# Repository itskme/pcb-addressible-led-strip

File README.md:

This is my first independent design using kiCAD. No tutorals or anything like that. I have not written software for this project however you should be able to adapt any rgb matrix program to control this board as-is, or modify the physical connections yourself if you want!

Gerbers are in the project directory

Enjoy :)

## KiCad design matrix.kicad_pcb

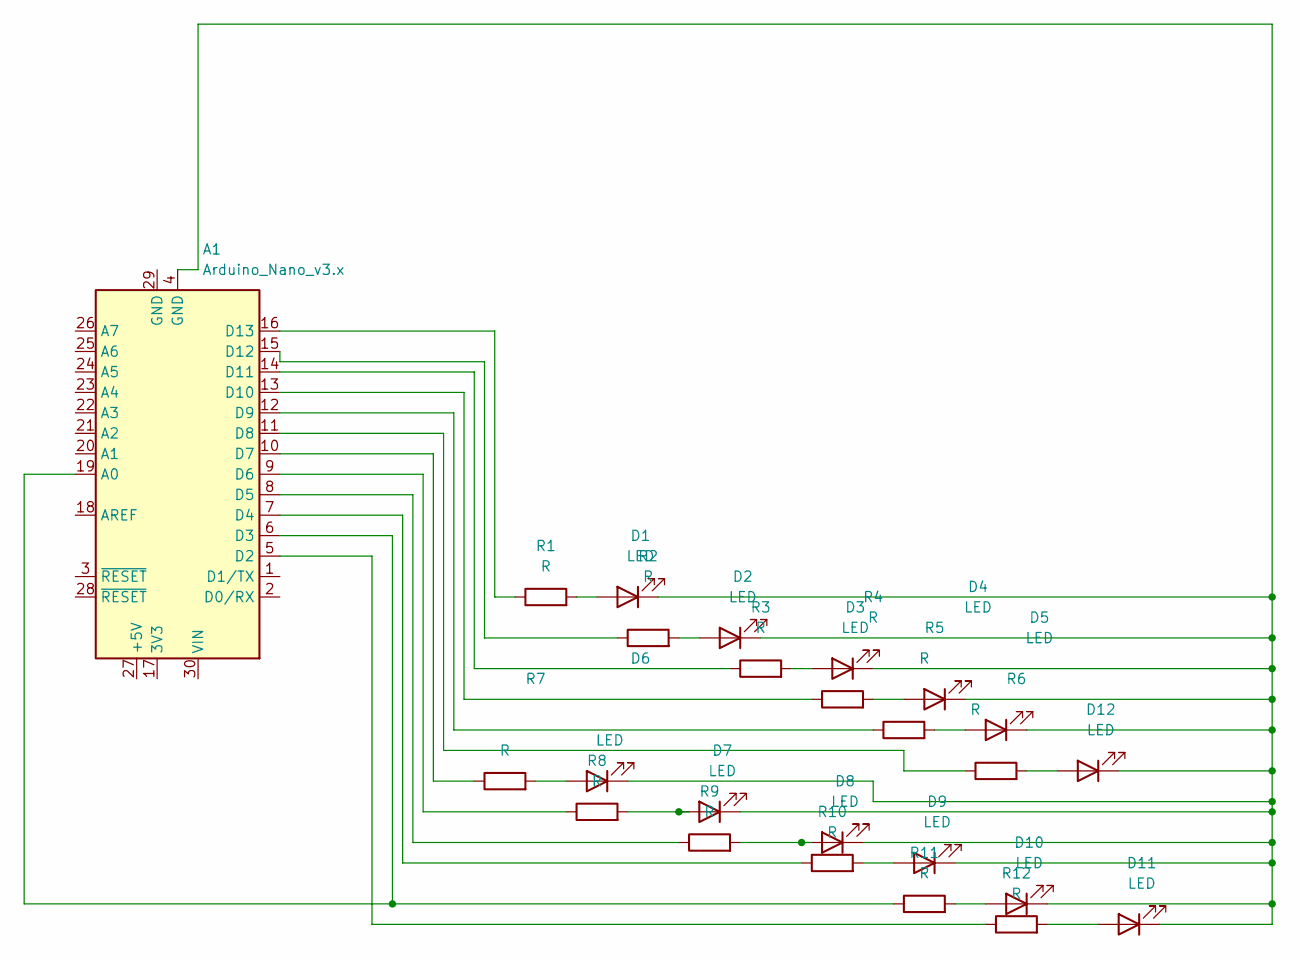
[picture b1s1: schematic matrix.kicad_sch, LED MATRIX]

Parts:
A1: Arduino_Nano_v3.x; Arduino_Nano
D1, D2, D3, D4, D5, D6, D7, D8, D9, D10, D11, D12: LED; LED_0402_1005Metric
R1, R2, R3, R4, R5, R6, R7, R8, R9, R10, R11, R12: R; R_01005_0402Metric

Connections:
unnamed: A1.6 (D3), A1.19 (A0), R11.1
unnamed: A1.5 (D2), R12.1
unnamed: A1.7 (D4), R10.1
unnamed: A1.8 (D5), R9.1
unnamed: A1.9 (D6), R8.1
unnamed: A1.10 (D7), R7.1
unnamed: A1.11 (D8), R6.1
unnamed: A1.12 (D9), R5.1
unnamed: A1.13 (D10), R4.1
unnamed: A1.14 (D11), R3.1
unnamed: A1.15 (D12), R2.1
unnamed: A1.16 (D13), R1.1
unnamed: D1.2 (A), R1.2
unnamed: A1.4 (GND), D1.1 (K), D2.1 (K), D3.1 (K), D4.1 (K), D5.1 (K), D6.1 (K), D7.1 (K), D8.1 (K), D9.1 (K), D10.1 (K), D11.1 (K), D12.1 (K)
unnamed: D2.2 (A), R2.2
unnamed: D3.2 (A), R3.2
unnamed: D4.2 (A), R4.2
unnamed: D5.2 (A), R5.2
unnamed: D6.2 (A), R7.2
unnamed: D7.2 (A), R8.2
unnamed: D8.2 (A), R9.2
unnamed: D9.2 (A), R10.2
unnamed: D10.2 (A), R11.2
unnamed: D11.2 (A), R12.2
unnamed: D12.2 (A), R6.2

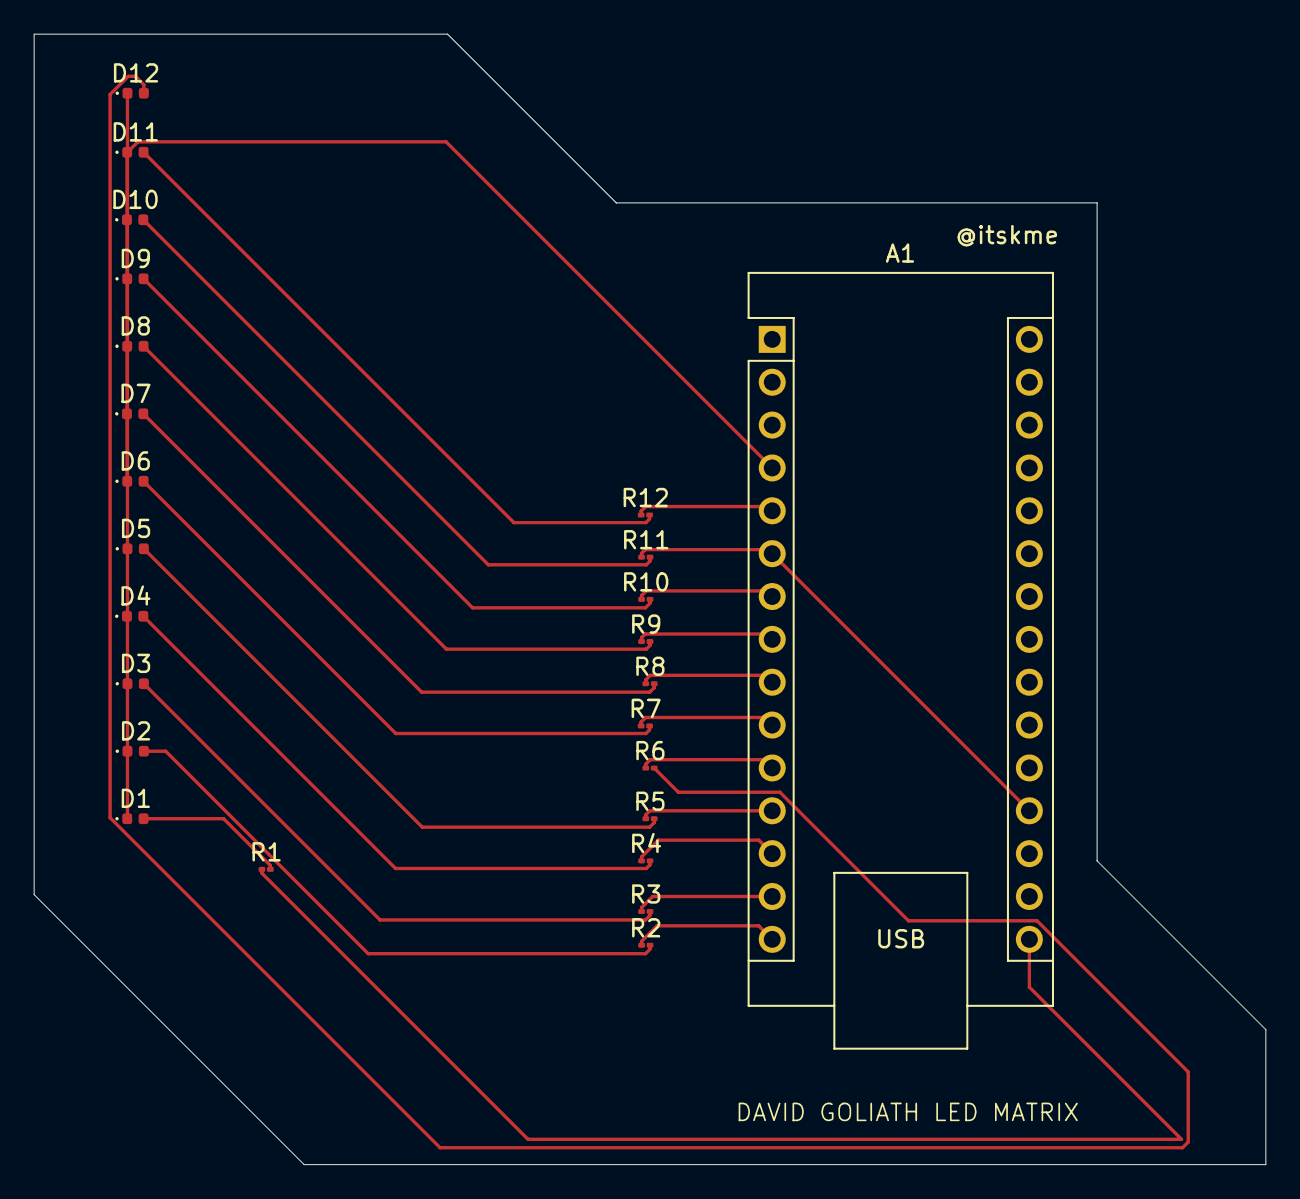
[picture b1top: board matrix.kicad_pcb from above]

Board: 2 copper layers, 73.0 x 67.0 mm, 25 parts (0 on the bottom side), 25 nets.

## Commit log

2024-07-14 Finished board
2024-08-30 Add modified files (good meta)+gerbers
